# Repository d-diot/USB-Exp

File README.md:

# USB-Exp

This board is part of the [d-diot project](https://www.d-diot.com)
See the dedicated [wiki page](https://wiki.d-diot.com/hardware/pcb/mysensors/usb-exp) to know more about this board.

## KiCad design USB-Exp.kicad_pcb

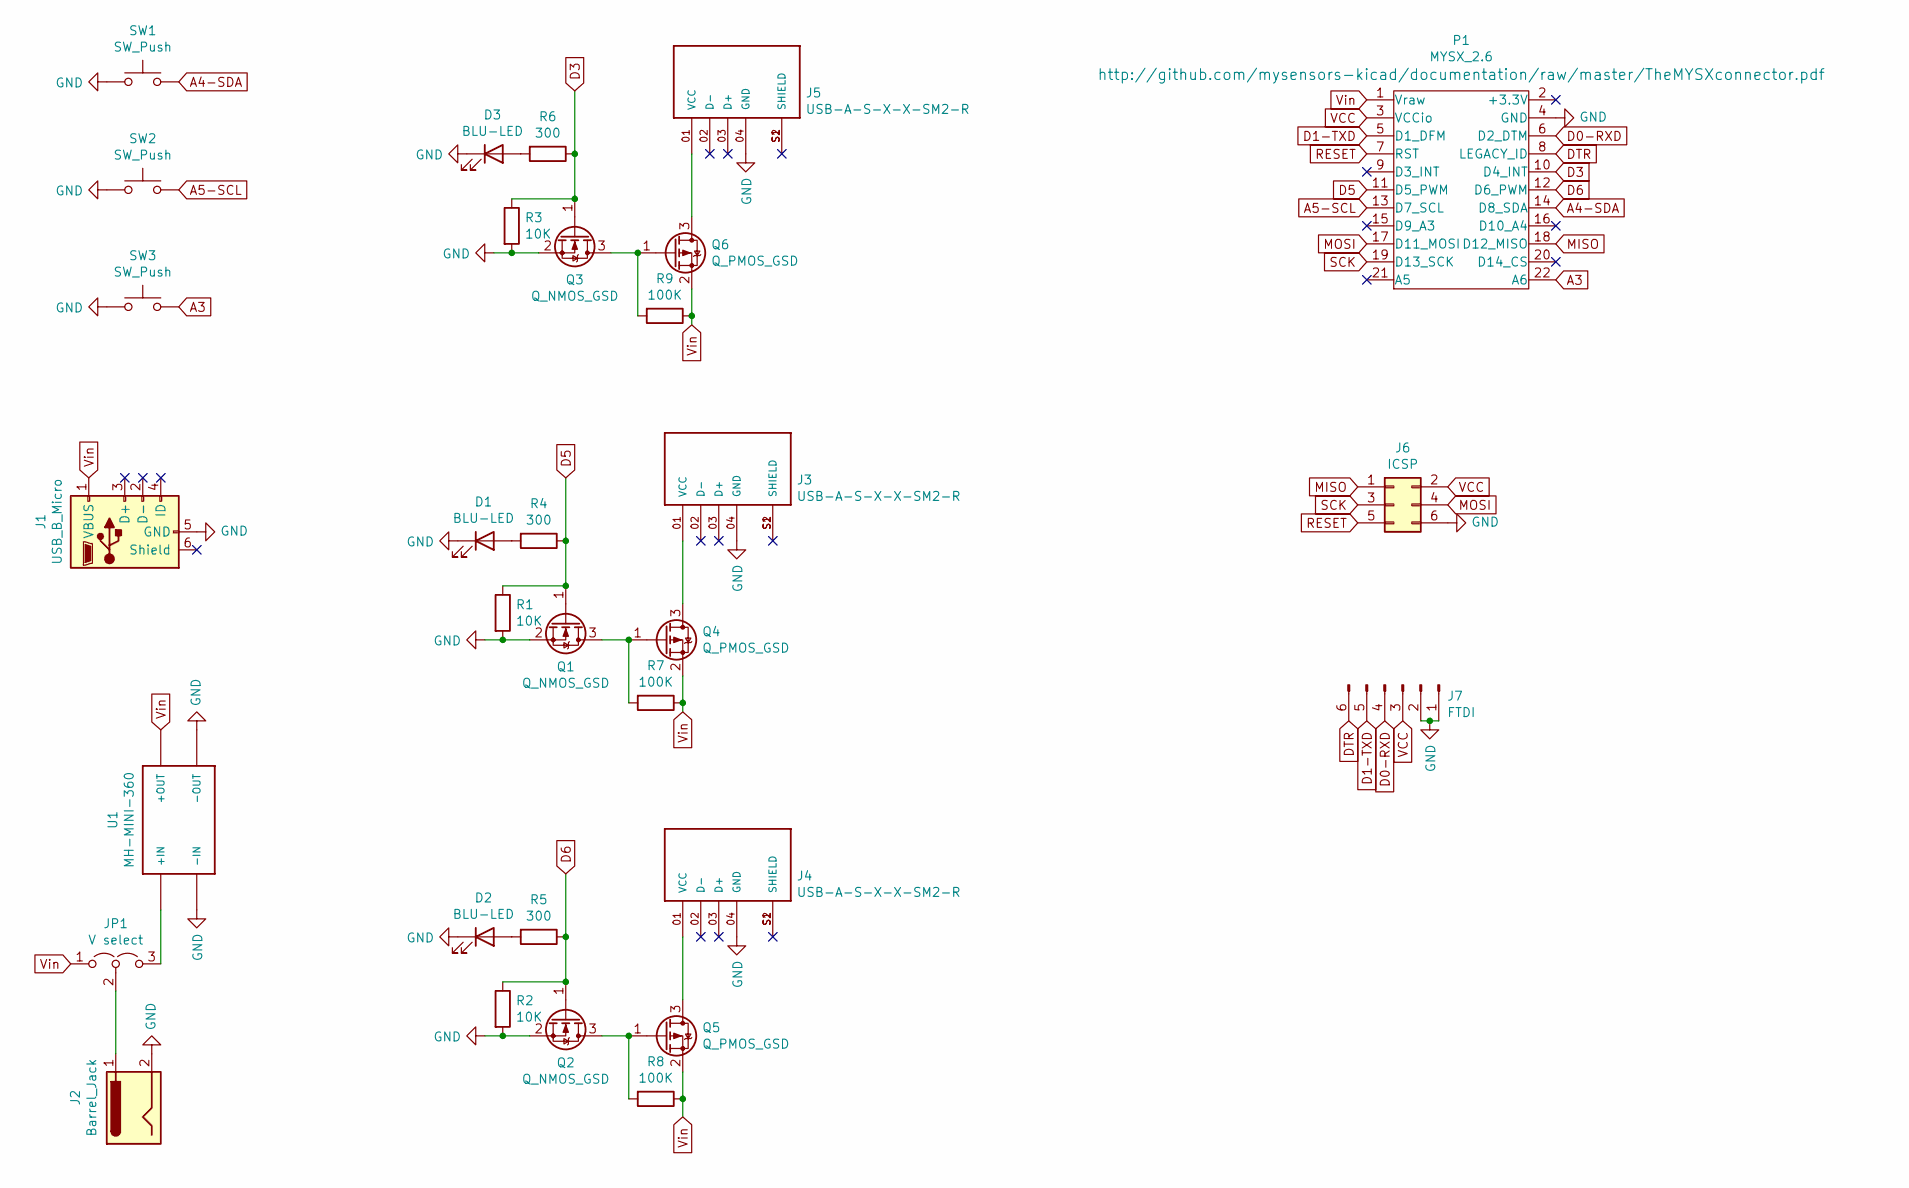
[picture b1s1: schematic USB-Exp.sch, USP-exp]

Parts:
D1, D2, D3: BLU-LED; LED_0805_2012Metric_Pad1.15x1.40mm_HandSolder; MPN NCD0805B2
J1: USB_B_Micro; USB_Micro-B_Molex-105017-0001; MPN C10418
J2: Barrel_Jack; BarrelJack_Wuerth_6941xx301002; MPN 694106301002
J3, J4, J5: USB-A-S-X-X-SM2-R; SAMTEC_USB-A-S-X-X-SM2-R; MPN YJ-USB-AF-SMT-01
J6: ICSP; PinHeader_2x03_P2.54mm_Vertical; MPN C65114
J7: FTDI; PinHeader_1x06_P2.54mm_Vertical; MPN Z-211-0611-0021-001
JP1: V select; PinHeader_1x03_P2.54mm_Vertical; MPN C49257
P1: MYSX_2.6; MYSX_2.6_SOCKET; MPN DS1023-2*11SF11
Q1, Q2, Q3: Q_NMOS_GSD; SOT-23; MPN JST2300
Q4, Q5, Q6: Q_PMOS_GSD; SOT-23; MPN JST3415C
R1, R2, R3: 10K; R_0805_2012Metric_Pad1.15x1.40mm_HandSolder; MPN TC0550F1002T5E
R4, R5, R6: 300; R_0805_2012Metric_Pad1.15x1.40mm_HandSolder; MPN TC0525F3000T5E
R7, R8, R9: 100K; R_0805_2012Metric_Pad1.15x1.40mm_HandSolder; MPN TC0525F1003T5E
SW1, SW2, SW3: SW_Push; SW_1437566-3; MPN NA
U1: MH-MINI-360; MPN Mini-360

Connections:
A3: P1.22 (A6), SW3.2
A4-SDA: P1.14 (D8_SDA), SW1.2
A5-SCL: P1.13 (D7_SCL), SW2.2
D0-RXD: J7.4, P1.6 (D2_DTM)
D1-TXD: J7.5, P1.5 (D1_DFM)
D3: P1.10 (D4_INT), Q3.1 (G), R3.1, R6.1
D5: P1.11 (D5_PWM), Q1.1 (G), R1.1, R4.1
D6: P1.12 (D6_PWM), Q2.1 (G), R2.1, R5.1
DTR: J7.6, P1.8 (LEGACY_ID)
GND: D1.1 (K), D2.1 (K), D3.1 (K), J1.5 (GND), J2.2, J3.04 (GND), J4.04 (GND), J5.04 (GND), J6.6, J7.1, J7.2, P1.4 (GND), Q1.2 (S), Q2.2 (S), Q3.2 (S), R1.2, R2.2, R3.2, SW1.1, SW2.1, SW3.1, U1.P$1 (-IN), U1.P$4 (-OUT)
MISO: J6.1, P1.18 (D12_MISO)
MOSI: J6.4, P1.17 (D11_MOSI)
unnamed: D1.2 (A), R4.2
unnamed: D2.2 (A), R5.2
unnamed: D3.2 (A), R6.2
unnamed: J2.1, JP1.2 (C)
unnamed: J3.01 (VCC), Q4.3 (D)
unnamed: J3.S1 (SHIELD), J3.S2 (SHIELD)
unnamed: J4.01 (VCC), Q5.3 (D)
unnamed: J4.S1 (SHIELD), J4.S2 (SHIELD)
unnamed: J5.01 (VCC), Q6.3 (D)
unnamed: J5.S1 (SHIELD), J5.S2 (SHIELD)
unnamed: JP1.3 (B), U1.P$2 (+IN)
unnamed: Q1.3 (D), Q4.1 (G), R7.2
unnamed: Q2.3 (D), Q5.1 (G), R8.2
unnamed: Q3.3 (D), Q6.1 (G), R9.2
RESET: J6.5, P1.7 (RST)
SCK: J6.3, P1.19 (D13_SCK)
VCC: J6.2, J7.3, P1.3 (VCCio)
Vin: J1.1 (VBUS), JP1.1 (A), P1.1 (Vraw), Q4.2 (S), Q5.2 (S), Q6.2 (S), R7.1, R8.1, R9.1, U1.P$3 (+OUT)

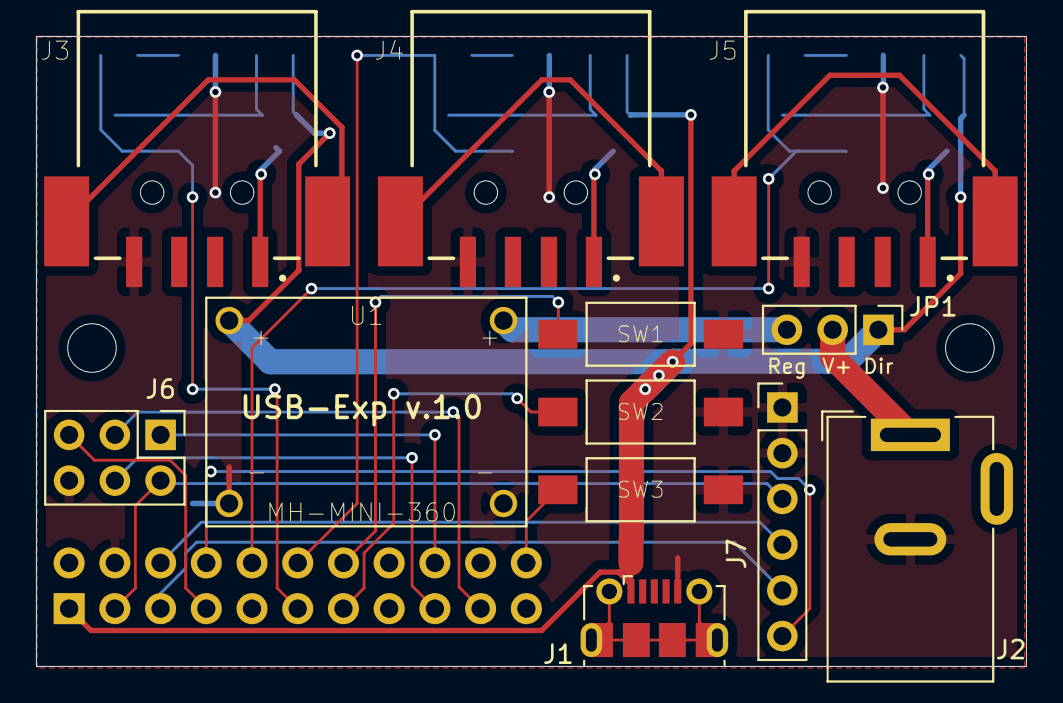
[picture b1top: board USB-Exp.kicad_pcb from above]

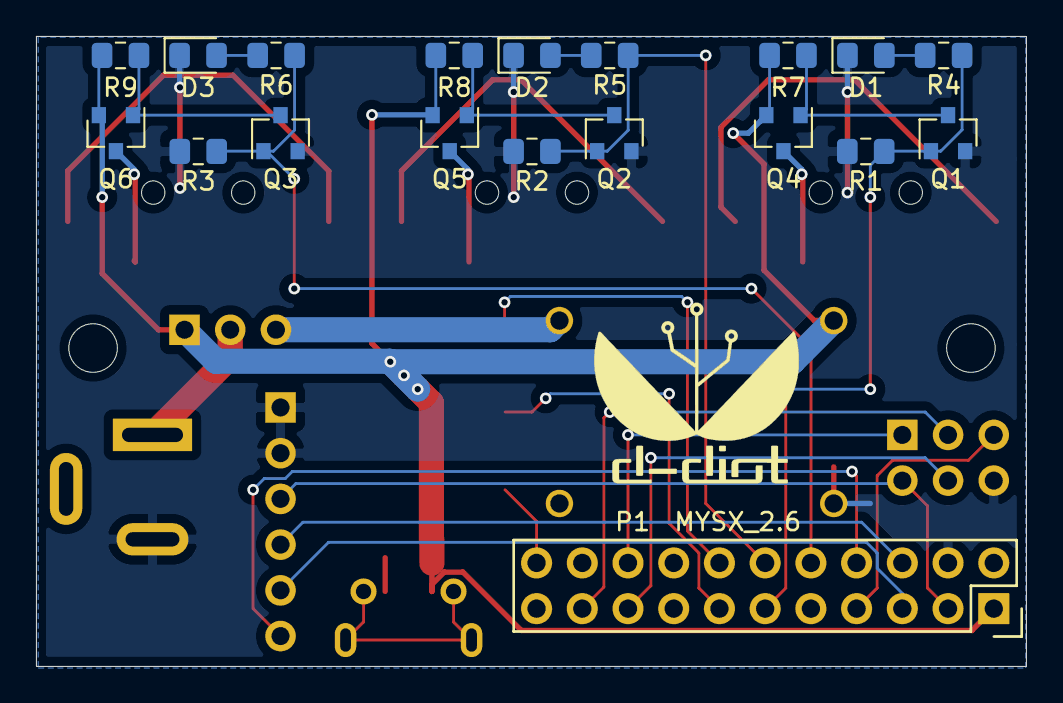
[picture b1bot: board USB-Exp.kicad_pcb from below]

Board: 2 copper layers, 55.0 x 35.0 mm, 31 parts (18 on the bottom side), 30 nets.

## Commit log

2020-06-20 USB-Exp first commit
2020-06-22 modified gerber files and added pdf of schematics
2020-07-14 fixed R, R8 and R9 connection
2020-10-25 Updated documentation and README-md
